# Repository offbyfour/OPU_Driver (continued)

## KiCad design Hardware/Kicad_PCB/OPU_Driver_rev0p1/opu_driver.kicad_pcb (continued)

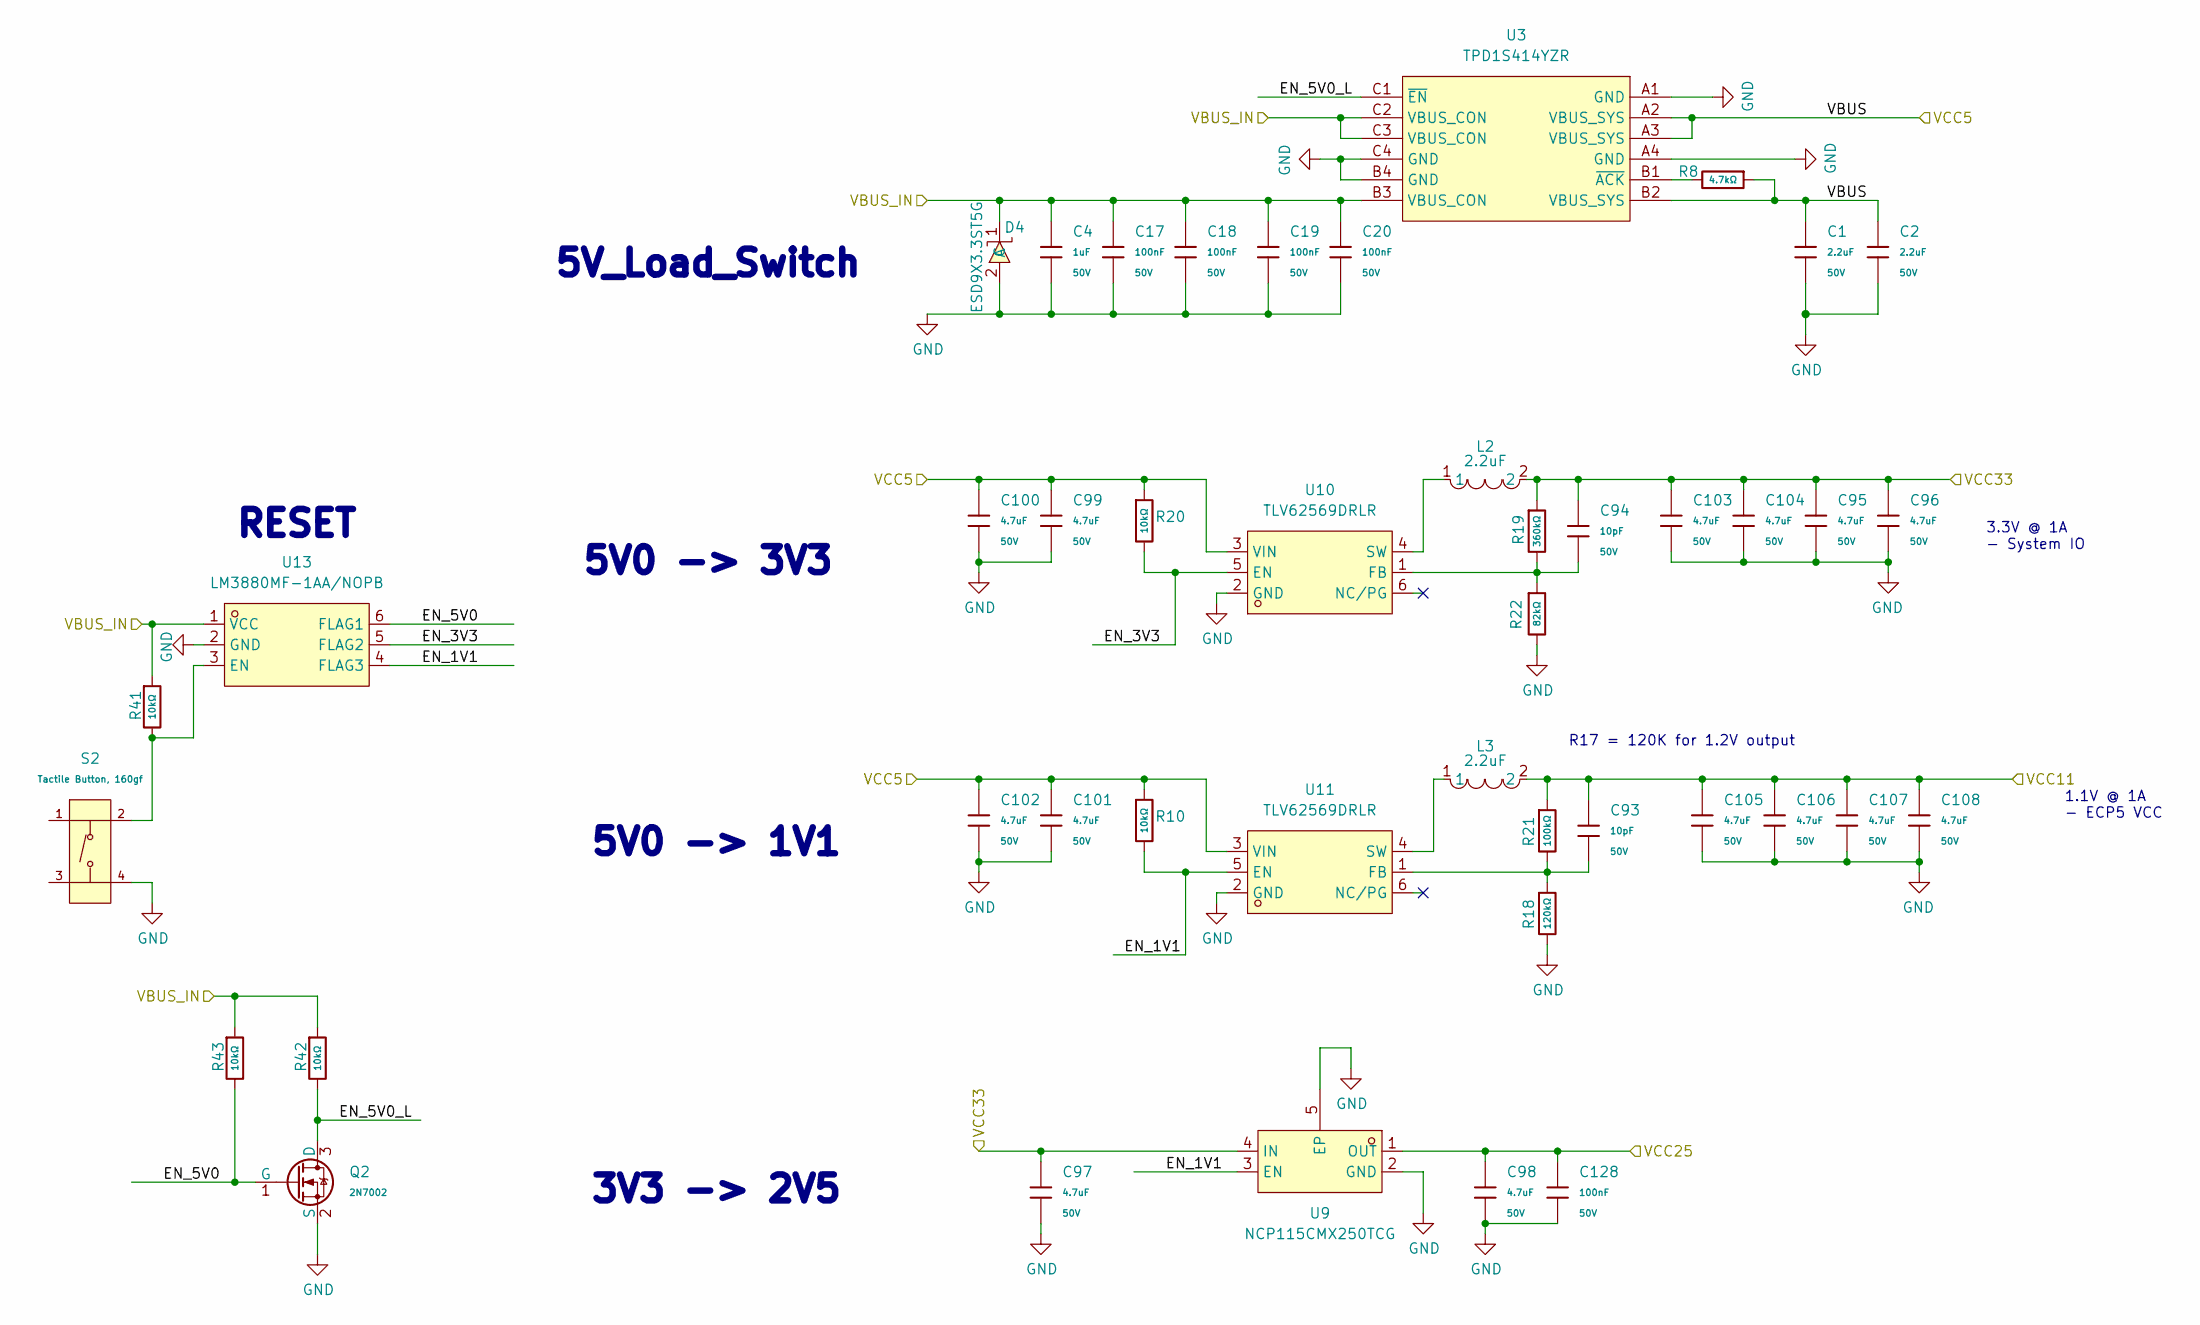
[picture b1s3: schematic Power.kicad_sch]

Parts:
C1, C2: 2.2uF; C_1206; Voltage Rated 50V; Tolerance ±10%; Part CL31B225KBHNNNE; LCSC C50254
C4: 1uF; C_0805; Voltage Rated 50V; Tolerance ±10%; Part CL21B105KBFNNNE; LCSC C28323
C17, C18, C19, C20, C128: 100nF; C_0402; Voltage Rated 50V; Tolerance ±10%; Part CL05B104KB54PNC; LCSC C307331
C93, C94: 10pF; C_0402; Voltage Rated 50V; Tolerance ±5%; Part CL05C100JB5NNNC; LCSC C32949
C95, C96, C97, C98, C99, C100, C101, C102, C103, C104, C105, C106, C107, C108: 4.7uF; C_1206; Voltage Rated 50V; Tolerance ±10%; Part 1206B475K500NT; LCSC C29823
D4: ESD9X3.3ST5G; SOD-923_L0.8-W0.6-LS1.0-RD; LCSC Part C130456
L2, L3: LQM21PN2R2NGCD; L0805; LCSC Part C86089
Q2: 2N7002; Q_SOT-23; Part 2N7002; LCSC C8545
R8: 4.7kΩ; R_0402; Overload Voltage (Max) 50V; Tolerance ±1%; Part 0402WGF4701TCE; LCSC C25900
R10, R20, R41, R42, R43: 10kΩ; R_0402; Overload Voltage (Max) 50V; Tolerance ±1%; Part 0402WGF1002TCE; LCSC C25744
R18: 120kΩ; R_0402; Overload Voltage (Max) 50V; Tolerance ±1%; Part 0402WGF1203TCE; LCSC C25750
R19: 360kΩ; R_0603; Overload Voltage (Max) 75V; Tolerance ±1%; Part 0603WAF3603T5E; LCSC C23146
R21: 100kΩ; R_0402; Overload Voltage (Max) 50V; Tolerance ±1%; Part 0402WGF1003TCE; LCSC C25741
R22: 82kΩ; R_0603; Overload Voltage (Max) 75V; Tolerance ±1%; Part 0603WAF8202T5E; LCSC C23254
S2: Tactile Button, 160gf; SW-SMD_4P-L5.1-W5.1-P3.70-LS6.5-TL-2; Voltage Rating (Dc) 12V; Part TS-1187A-B-A-B; LCSC C318884
U3: TPD1S414YZR; DSBGA-12_L1.9-W1.4-R3-C4-P0.40-TL; LCSC Part C411873
U9: NCP115CMX250TCG; XDFN-4_L1.0-W1.0-P0.65-BL-EP; LCSC Part C603508
U10, U11: TLV62569DRLR; SOT-563_L1.6-W1.2-P0.50-LS1.6-BL; LCSC Part C163217
U13: LM3880MF-1AA/NOPB; SOT-23-6_L2.9-W1.6-P0.95-LS2.8-BR; LCSC Part C486059

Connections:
+1V1: C93.1, C105.1, C106.1, C107.1, C108.1, L3.2, R21.1; also elsewhere on the board
+2V5: C98.1, C128.1, U9.1 (OUT); also elsewhere on the board
+3V3: C94.1, C95.1, C96.1, C97.1, C103.1, C104.1, L2.2, R19.1, U9.4 (IN); also elsewhere on the board
/Power/EN_1V1: R10.2, U9.3 (EN), U11.5 (EN), U13.4 (FLAG3)
/Power/EN_3V3: R20.2, U10.5 (EN), U13.5 (FLAG2)
/Power/EN_5V0: Q2.1 (G), R43.2, U13.6 (FLAG1)
/Power/EN_5V0_L: Q2.3 (D), R42.2, U3.C1 (~EN)
/VBUS: C4.1, C17.1, C18.1, C19.1, C20.1, D4.1 (C), R41.1, R42.1, R43.1, U3.B3 (VBUS_CON), U3.C2 (VBUS_CON), U3.C3 (VBUS_CON), U13.1 (VCC); also elsewhere on the board
GND: C1.2, C2.2, C4.2, C17.2, C18.2, C19.2, C20.2, C95.2, C96.2, C97.2, C98.2, C99.2, C100.2, C101.2, C102.2, C103.2, C104.2, C105.2, C106.2, C107.2, C108.2, C128.2, D4.2 (A), Q2.2 (S), R18.2, R22.2, S2.4 (D), U3.A1 (GND), U3.A4 (GND), U3.B4 (GND), U3.C4 (GND), U9.2 (GND), U9.5 (EP), U10.2 (GND), U11.2 (GND), U13.2 (GND); also elsewhere on the board
unnamed: R41.2, S2.2 (B), U13.3 (EN)
unnamed: R8.2, U3.B1 (~ACK)
unnamed: C94.2, R19.2, R22.1, U10.1 (FB)
unnamed: L2.1, U10.4 (SW)
unnamed: C93.2, R18.1, R21.2, U11.1 (FB)
unnamed: L3.1, U11.4 (SW)

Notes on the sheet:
3.3V @ 1A - System IO
5V0 -> 1V1
RESET
5V_Load_Switch
1.1V @ 1A - ECP5 VCC
5V0 -> 3V3
3V3 -> 2V5
R17 = 120K for 1.2V output

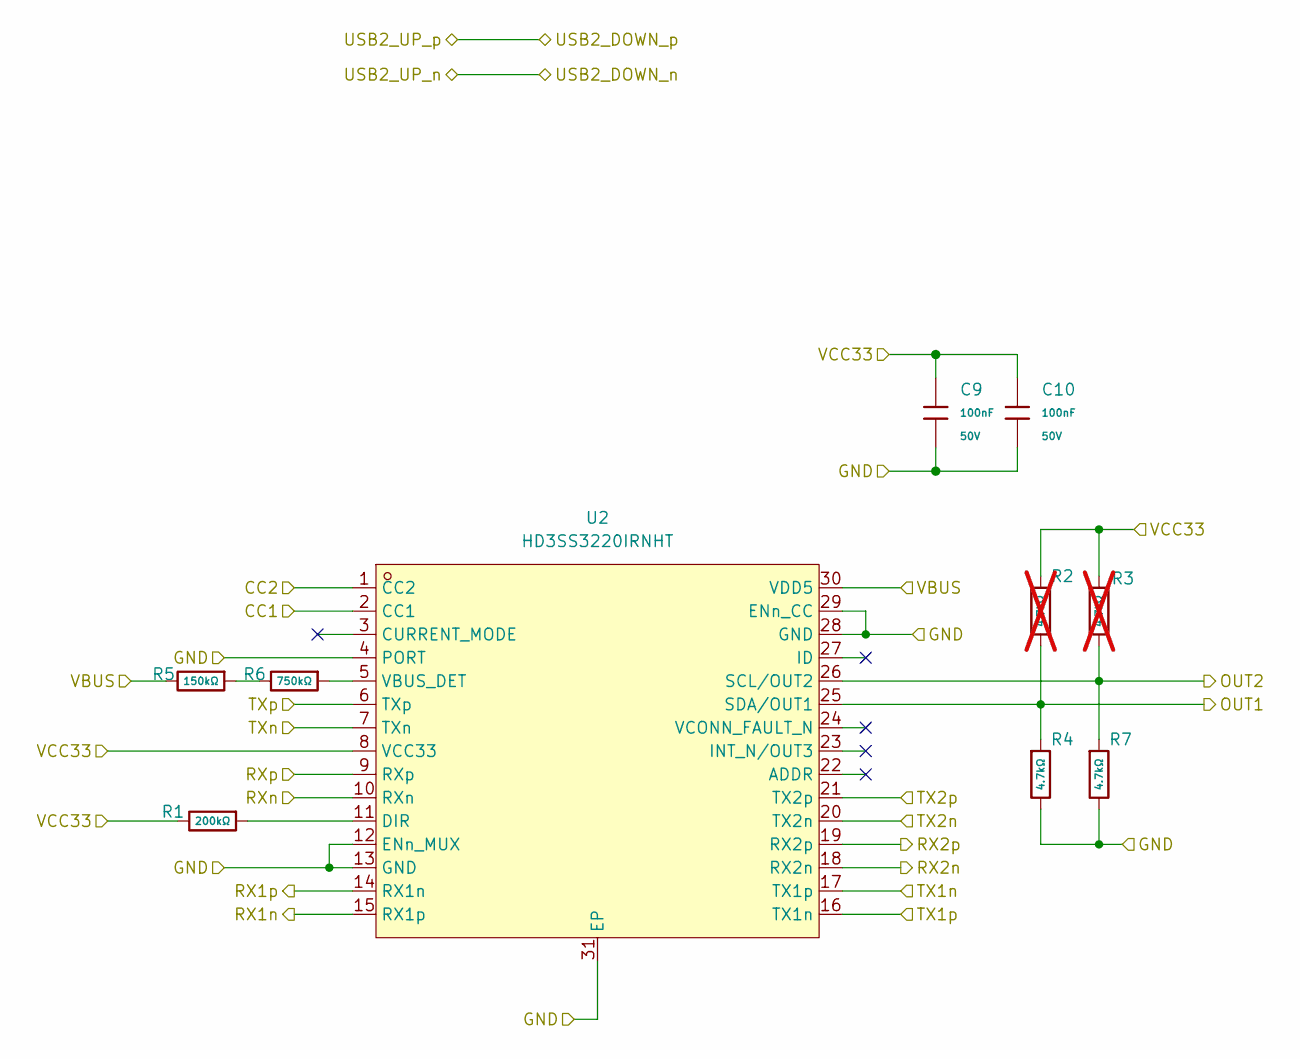
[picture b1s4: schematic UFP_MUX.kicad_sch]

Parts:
C9, C10: 100nF; C_0402; Voltage Rated 50V; Tolerance ±10%; Part CL05B104KB54PNC; LCSC C307331
R1: 200kΩ; R_0402; Overload Voltage (Max) 50V; Tolerance ±1%; Part 0402WGF2003TCE; LCSC C25764
R2, R3: 4.7kΩ; R_0402; Overload Voltage (Max) 50V; Tolerance ±1%; Part 0402WGF4701TCE; LCSC C25900; not fitted
R4, R7: 4.7kΩ; R_0402; Overload Voltage (Max) 50V; Tolerance ±1%; Part 0402WGF4701TCE; LCSC C25900
R5: 150kΩ; R_0402; Overload Voltage (Max) 50V; Tolerance ±1%; Part 0402WGF1503TCE; LCSC C25755
R6: 750kΩ; R_0603; Overload Voltage (Max) 75V; Tolerance ±1%; Part 0603WAF7503T5E; LCSC C23240
U2: HD3SS3220IRNHT; WQFN-30_L4.5-W2.5-P0.4-BL-EP; LCSC Part C2876685

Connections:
+3V3: C9.1, C10.1, R1.2, R2.1, R3.1, U2.8 (VCC33); also elsewhere on the board
/CC1: U2.2 (CC1); also elsewhere on the board
/CC2: U2.1 (CC2); also elsewhere on the board
/RX1+: U2.14 (RX1n); also elsewhere on the board
/RX1-: U2.15 (RX1p); also elsewhere on the board
/RX2+: U2.19 (RX2p); also elsewhere on the board
/RX2-: U2.18 (RX2n); also elsewhere on the board
/RXN: U2.10 (RXn); also elsewhere on the board
/RXP: U2.9 (RXp); also elsewhere on the board
/TX1_N: U2.17 (TX1p); also elsewhere on the board
/TX1_P: U2.16 (TX1n); also elsewhere on the board
/TX2_N: U2.20 (TX2n); also elsewhere on the board
/TX2_P: U2.21 (TX2p); also elsewhere on the board
/TXpre_N: U2.7 (TXn); also elsewhere on the board
/TXpre_P: U2.6 (TXp); also elsewhere on the board
/UFP_MUX/OUT1: R2.2, R4.1, U2.25 (SDA/OUT1)
/UFP_MUX/OUT2: R3.2, R7.1, U2.26 (SCL/OUT2)
GND: C9.2, C10.2, R4.2, R7.2, U2.4 (PORT), U2.12 (ENn_MUX), U2.13 (GND), U2.28 (GND), U2.29 (ENn_CC), U2.31 (EP); also elsewhere on the board
unnamed: R5.1, R6.2
unnamed: R1.1, U2.11 (DIR)
unnamed: R6.1, U2.5 (VBUS_DET)

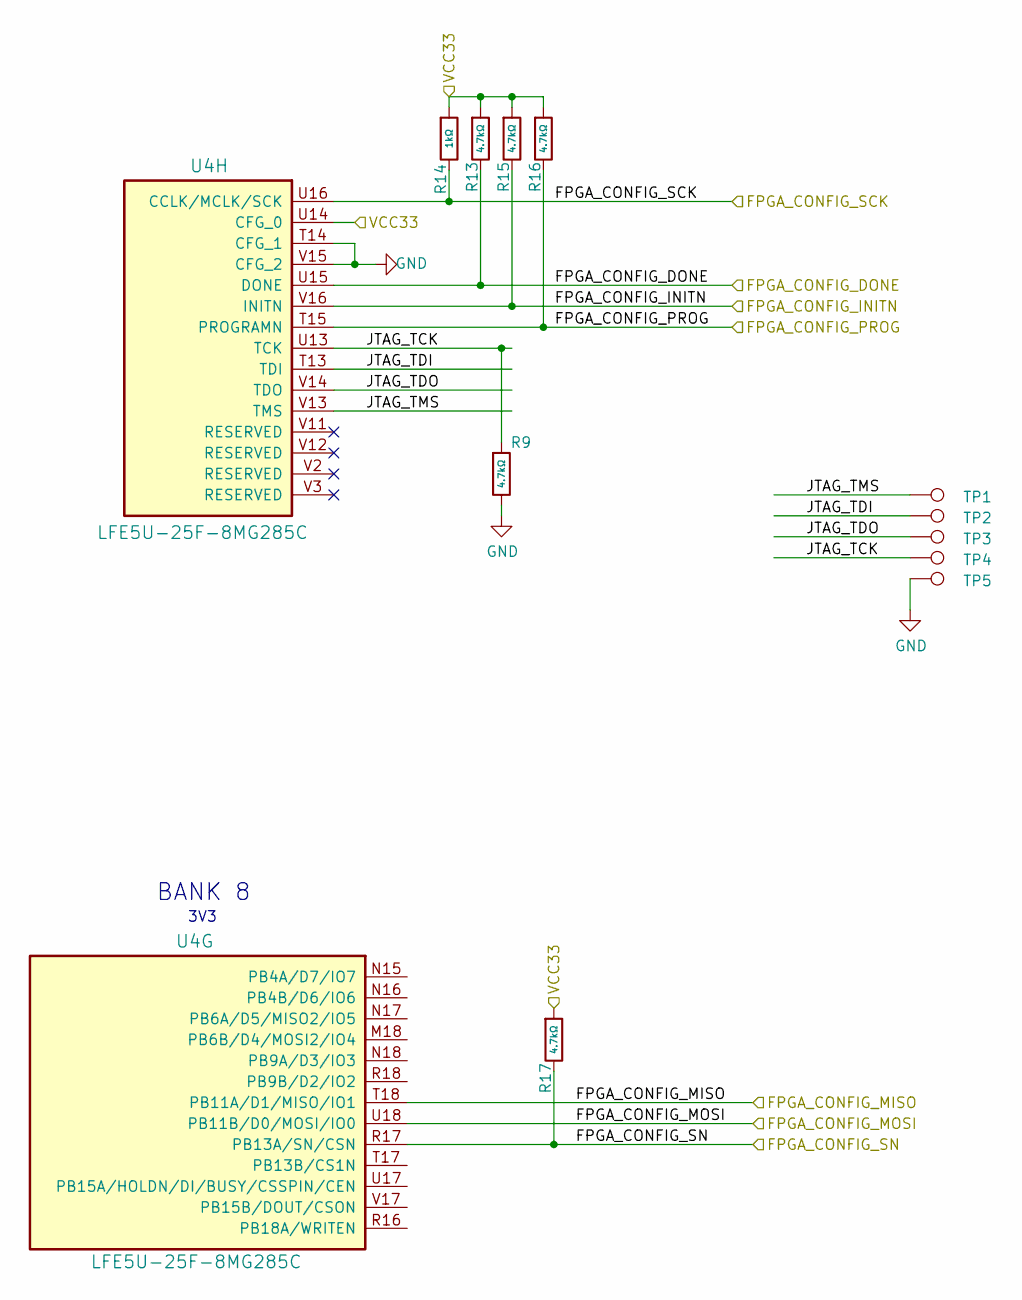
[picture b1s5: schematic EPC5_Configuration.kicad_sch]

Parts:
R9, R13, R15, R16, R17: 4.7kΩ; R_0402; Overload Voltage (Max) 50V; Tolerance ±1%; Part 0402WGF4701TCE; LCSC C25900
R14: 1kΩ; R_0402; Overload Voltage (Max) 50V; Tolerance ±1%; Part 0402WGF1001TCE; LCSC C11702
TP1, TP2, TP3, TP4, TP5: TestPoint; TestPoint_Pad_D1.0mm
U4: LFE5U-25F-8MG285C; csBGA285

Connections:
+3V3: R13.1, R14.1, R15.1, R16.1, R17.1, U4.U14 (CFG_0); also elsewhere on the board
/EPC5_Configuration/JTAG_TCK: R9.1, TP4.1, U4.U13 (TCK)
/EPC5_Configuration/JTAG_TDI: TP2.1, U4.T13 (TDI)
/EPC5_Configuration/JTAG_TDO: TP3.1, U4.V14 (TDO)
/EPC5_Configuration/JTAG_TMS: TP1.1, U4.V13 (TMS)
/FPGA_CONFIG_DONE: R13.2, U4.U15 (DONE); also elsewhere on the board
/FPGA_CONFIG_INITN: R15.2, U4.V16 (INITN); also elsewhere on the board
/FPGA_CONFIG_MISO: U4.T18 (PB11A/D1/MISO/IO1); also elsewhere on the board
/FPGA_CONFIG_MOSI: U4.U18 (PB11B/D0/MOSI/IO0); also elsewhere on the board
/FPGA_CONFIG_PROG: R16.2, U4.T15 (PROGRAMN); also elsewhere on the board
/FPGA_CONFIG_SCK: R14.2, U4.U16 (CCLK/MCLK/SCK); also elsewhere on the board
/FPGA_CONFIG_SN: R17.2, U4.R17 (PB13A/SN/CSN); also elsewhere on the board
GND: R9.2, TP5.1, U4.T14 (CFG_1), U4.V15 (CFG_2); also elsewhere on the board

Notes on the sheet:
BANK 8
3V3

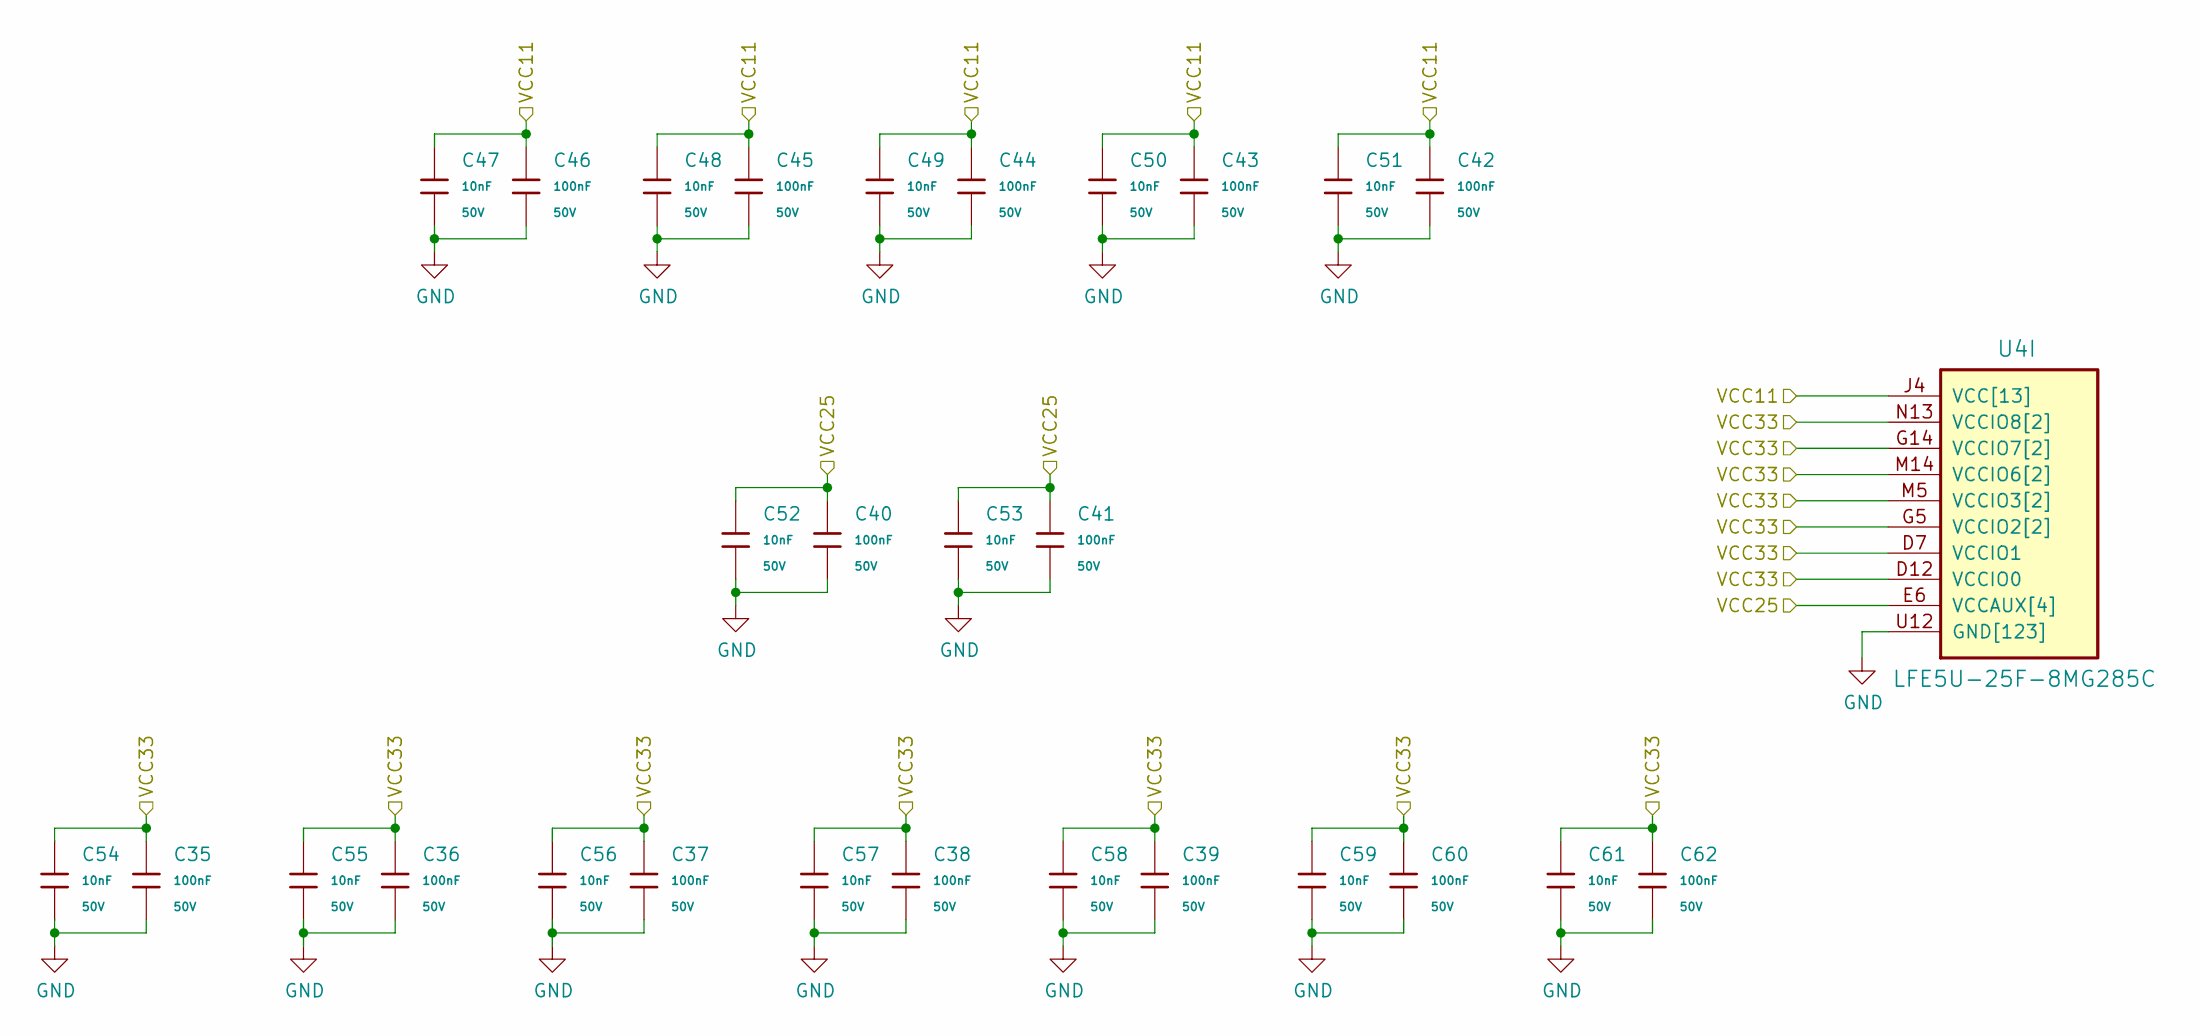
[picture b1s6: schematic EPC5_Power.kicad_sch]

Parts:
C35, C36, C37, C38, C39, C40, C41, C42, C43, C44, C45, C46, C60, C62: 100nF; C_0402; Voltage Rated 50V; Tolerance ±10%; Part CL05B104KB54PNC; LCSC C307331
C47, C48, C49, C50, C51, C52, C53, C54, C55, C56, C57, C58, C59, C61: 10nF; C_0402; Voltage Rated 50V; Tolerance ±10%; Part CL05B103KB5NNNC; LCSC C15195
U4: LFE5U-25F-8MG285C; csBGA285

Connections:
+1V1: C42.1, C43.1, C44.1, C45.1, C46.1, C47.1, C48.1, C49.1, C50.1, C51.1, U4.D8 (VCC[13]), U4.D9 (VCC[13]), U4.D10 (VCC[13]), U4.D11 (VCC[13]), U4.J4 (VCC[13]), U4.J5 (VCC[13]), U4.J14 (VCC[13]), U4.J15 (VCC[13]), U4.M4 (VCC[13]), U4.M15 (VCC[13]), U4.P7 (VCC[13]), U4.P9 (VCC[13]), U4.P11 (VCC[13]); also elsewhere on the board
+2V5: C40.1, C41.1, C52.1, C53.1, U4.E6 (VCCAUX[4]), U4.E13 (VCCAUX[4]), U4.N6 (VCCAUX[4]), U4.P13 (VCCAUX[4]); also elsewhere on the board
+3V3: C35.1, C36.1, C37.1, C38.1, C39.1, C54.1, C55.1, C56.1, C57.1, C58.1, C59.1, C60.1, C61.1, C62.1, U4.D7 (VCCIO1), U4.D12 (VCCIO0), U4.G5 (VCCIO2[2]), U4.G14 (VCCIO7[2]), U4.H5 (VCCIO2[2]), U4.H14 (VCCIO7[2]), U4.M5 (VCCIO3[2]), U4.M14 (VCCIO6[2]), U4.N5 (VCCIO3[2]), U4.N13 (VCCIO8[2]), U4.N14 (VCCIO6[2]), U4.P14 (VCCIO8[2]); also elsewhere on the board
GND: C35.2, C36.2, C37.2, C38.2, C39.2, C40.2, C41.2, C42.2, C43.2, C44.2, C45.2, C46.2, C47.2, C48.2, C49.2, C50.2, C51.2, C52.2, C53.2, C54.2, C55.2, C56.2, C57.2, C58.2, C59.2, C60.2, C61.2, C62.2, U4.B3 (GND[123]), U4.B16 (GND[123]), U4.E5 (GND[123]), U4.E7 (GND[123]), U4.E8 (GND[123]), U4.E9 (GND[123]), U4.E10 (GND[123]), U4.E11 (GND[123]), U4.E12 (GND[123]), U4.E14 (GND[123]), U4.F5 (GND[123]), U4.F6 (GND[123]), U4.F7 (GND[123]), U4.F8 (GND[123]), U4.F9 (GND[123]), U4.F10 (GND[123]), U4.F11 (GND[123]), U4.F12 (GND[123]), U4.F13 (GND[123]), U4.F14 (GND[123]), U4.G2 (GND[123]), U4.G6 (GND[123]), U4.G7 (GND[123]), U4.G8 (GND[123]), U4.G9 (GND[123]), U4.G10 (GND[123]), U4.G11 (GND[123]), U4.G12 (GND[123]), U4.G13 (GND[123]), U4.G17 (GND[123]), U4.H6 (GND[123]), U4.H7 (GND[123]), U4.H8 (GND[123]), U4.H9 (GND[123]), U4.H10 (GND[123]), U4.H11 (GND[123]), U4.H12 (GND[123]), U4.H13 (GND[123]), U4.J6 (GND[123]), U4.J7 (GND[123]), U4.J8 (GND[123]), U4.J9 (GND[123]), U4.J10 (GND[123]), U4.J11 (GND[123]), U4.J12 (GND[123]), U4.J13 (GND[123]), U4.K5 (GND[123]), U4.K6 (GND[123]), U4.K7 (GND[123]), U4.K8 (GND[123]), U4.K9 (GND[123]), U4.K10 (GND[123]), U4.K11 (GND[123]), U4.K12 (GND[123]), U4.K13 (GND[123]), U4.K14 (GND[123]), U4.L2 (GND[123]), U4.L5 (GND[123]), U4.L6 (GND[123]), U4.L7 (GND[123]), U4.L8 (GND[123]), U4.L9 (GND[123]), U4.L10 (GND[123]), U4.L11 (GND[123]), U4.L12 (GND[123]), U4.L13 (GND[123]), U4.L14 (GND[123]), U4.L17 (GND[123]), U4.M6 (GND[123]), U4.M7 (GND[123]), U4.M8 (GND[123]), U4.M9 (GND[123]), U4.M10 (GND[123]), U4.M11 (GND[123]), U4.M12 (GND[123]), U4.M13 (GND[123]), U4.N7 (GND[123]), U4.N8 (GND[123]), U4.N9 (GND[123]), U4.N10 (GND[123]), U4.N11 (GND[123]), U4.N12 (GND[123]), U4.P5 (GND[123]), U4.P6 (GND[123]), U4.P8 (GND[123]), U4.P10 (GND[123]), U4.P12 (GND[123]), U4.R1 (GND[123]), U4.R2 (GND[123]), U4.R3 (GND[123]), U4.R10 (GND[123]), U4.T1 (GND[123]), U4.T2 (GND[123]), U4.T3 (GND[123]), U4.T4 (GND[123]), U4.T5 (GND[123]), U4.T6 (GND[123]), U4.T7 (GND[123]), U4.T8 (GND[123]), U4.T9 (GND[123]), U4.T10 (GND[123]), U4.T11 (GND[123]), U4.T12 (GND[123]), U4.T16 (GND[123]), U4.U1 (GND[123]), U4.U2 (GND[123]), U4.U3 (GND[123]), U4.U4 (GND[123]), U4.U5 (GND[123]), U4.U6 (GND[123]), U4.U7 (GND[123]), U4.U8 (GND[123]), U4.U9 (GND[123]), U4.U10 (GND[123]), U4.U11 (GND[123]), U4.U12 (GND[123]), U4.V4 (GND[123]), U4.V5 (GND[123]), U4.V6 (GND[123]), U4.V7 (GND[123]), U4.V8 (GND[123]), U4.V9 (GND[123]), U4.V10 (GND[123]); also elsewhere on the board

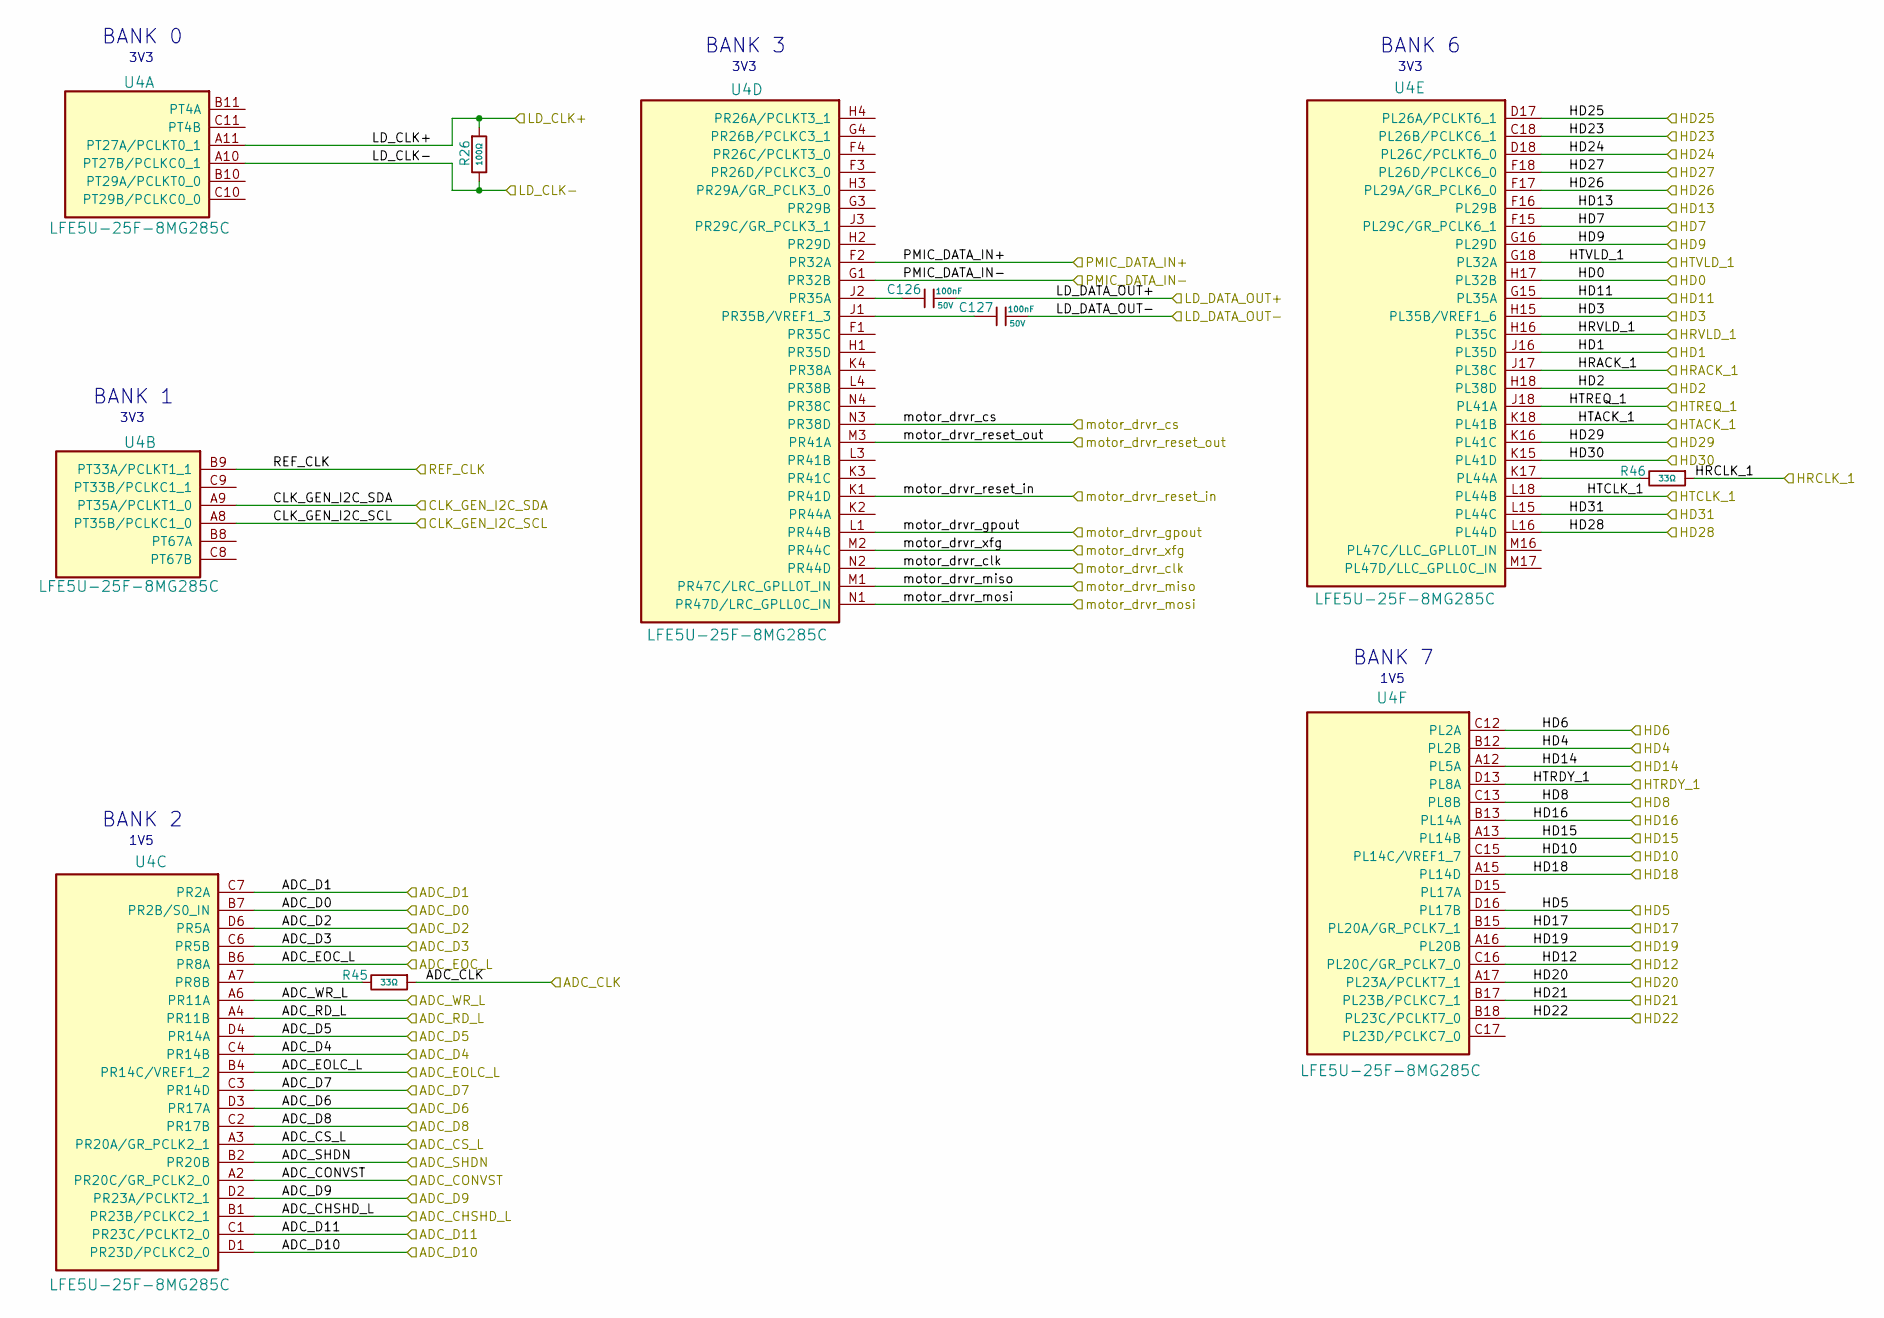
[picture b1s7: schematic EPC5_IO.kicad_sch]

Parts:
C126, C127: 100nF; C_0402; Voltage Rated 50V; Tolerance ±10%; Part CL05B104KB54PNC; LCSC C307331
R26: 100Ω; R_0402; Overload Voltage (Max) 50V; Tolerance ±1%; Part 0402WGF1000TCE; LCSC C25076
R45, R46: 33Ω; R_0402; Overload Voltage (Max) 50V; Tolerance ±1%; Part 0402WGF330JTCE; LCSC C25105
U4: LFE5U-25F-8MG285C; csBGA285

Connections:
/ADC_CHSHD_L: U4.B1 (PR23B/PCLKC2_1); also elsewhere on the board
/ADC_CLK: R45.1; also elsewhere on the board
/ADC_CONVST: U4.A2 (PR20C/GR_PCLK2_0); also elsewhere on the board
/ADC_CS_L: U4.A3 (PR20A/GR_PCLK2_1); also elsewhere on the board
/ADC_D0: U4.B7 (PR2B/S0_IN); also elsewhere on the board
/ADC_D1: U4.C7 (PR2A); also elsewhere on the board
/ADC_D2: U4.D6 (PR5A); also elsewhere on the board
/ADC_D3: U4.C6 (PR5B); also elsewhere on the board
/ADC_D4: U4.C4 (PR14B); also elsewhere on the board
/ADC_D5: U4.D4 (PR14A); also elsewhere on the board
/ADC_D6: U4.D3 (PR17A); also elsewhere on the board
/ADC_D7: U4.C3 (PR14D); also elsewhere on the board
/ADC_D8: U4.C2 (PR17B); also elsewhere on the board
/ADC_D9: U4.D2 (PR23A/PCLKT2_1); also elsewhere on the board
/ADC_D10: U4.D1 (PR23D/PCLKC2_0); also elsewhere on the board
/ADC_D11: U4.C1 (PR23C/PCLKT2_0); also elsewhere on the board
/ADC_EOC_L: U4.B6 (PR8A); also elsewhere on the board
/ADC_EOLC_L: U4.B4 (PR14C/VREF1_2); also elsewhere on the board
/ADC_RD_L: U4.A4 (PR11B); also elsewhere on the board
/ADC_SHDN: U4.B2 (PR20B); also elsewhere on the board
/ADC_WR_L: U4.A6 (PR11A); also elsewhere on the board
/CLK_GEN_I2C_SCL: U4.A8 (PT35B/PCLKC1_0); also elsewhere on the board
/CLK_GEN_I2C_SDA: U4.A9 (PT35A/PCLKT1_0); also elsewhere on the board
/HD0: U4.H17 (PL32B); also elsewhere on the board
/HD1: U4.J16 (PL35D); also elsewhere on the board
/HD2: U4.H18 (PL38D); also elsewhere on the board
/HD3: U4.H15 (PL35B/VREF1_6); also elsewhere on the board
/HD4: U4.B12 (PL2B); also elsewhere on the board
/HD5: U4.D16 (PL17B); also elsewhere on the board
/HD6: U4.C12 (PL2A); also elsewhere on the board
/HD7: U4.F15 (PL29C/GR_PCLK6_1); also elsewhere on the board
/HD8: U4.C13 (PL8B); also elsewhere on the board
/HD9: U4.G16 (PL29D); also elsewhere on the board
/HD10: U4.C15 (PL14C/VREF1_7); also elsewhere on the board
/HD11: U4.G15 (PL35A); also elsewhere on the board
/HD12: U4.C16 (PL20C/GR_PCLK7_0); also elsewhere on the board
/HD13: U4.F16 (PL29B); also elsewhere on the board
/HD14: U4.A12 (PL5A); also elsewhere on the board
/HD15: U4.A13 (PL14B); also elsewhere on the board
/HD16: U4.B13 (PL14A); also elsewhere on the board
/HD17: U4.B15 (PL20A/GR_PCLK7_1); also elsewhere on the board
/HD18: U4.A15 (PL14D); also elsewhere on the board
/HD19: U4.A16 (PL20B); also elsewhere on the board
/HD20: U4.A17 (PL23A/PCLKT7_1); also elsewhere on the board
/HD21: U4.B17 (PL23B/PCLKC7_1); also elsewhere on the board
/HD22: U4.B18 (PL23C/PCLKT7_0); also elsewhere on the board
/HD23: U4.C18 (PL26B/PCLKC6_1); also elsewhere on the board
/HD24: U4.D18 (PL26C/PCLKT6_0); also elsewhere on the board
/HD25: U4.D17 (PL26A/PCLKT6_1); also elsewhere on the board
/HD26: U4.F17 (PL29A/GR_PCLK6_0); also elsewhere on the board
/HD27: U4.F18 (PL26D/PCLKC6_0); also elsewhere on the board
/HD28: U4.L16 (PL44D); also elsewhere on the board
/HD29: U4.K16 (PL41C); also elsewhere on the board
/HD30: U4.K15 (PL41D); also elsewhere on the board
/HD31: U4.L15 (PL44C); also elsewhere on the board
/HRACK_1: U4.J17 (PL38C); also elsewhere on the board
/HRCLK_1: R46.1; also elsewhere on the board
/HRVLD_1: U4.H16 (PL35C); also elsewhere on the board
/HTACK_1: U4.K18 (PL41B); also elsewhere on the board
/HTCLK_1: U4.L18 (PL44B); also elsewhere on the board
/HTRDY_1: U4.D13 (PL8A); also elsewhere on the board
/HTREQ_1: U4.J18 (PL41A); also elsewhere on the board
/HTVLD_1: U4.G18 (PL32A); also elsewhere on the board
/LD_CLK+: R26.1, U4.A11 (PT27A/PCLKT0_1); also elsewhere on the board
/LD_CLK-: R26.2, U4.A10 (PT27B/PCLKC0_1); also elsewhere on the board
/LD_DATA_OUT+: C126.2; also elsewhere on the board
/LD_DATA_OUT-: C127.2; also elsewhere on the board
/PMIC_DATA_IN+: U4.F2 (PR32A); also elsewhere on the board
/PMIC_DATA_IN-: U4.G1 (PR32B); also elsewhere on the board
/motor_drvr_clk: U4.N2 (PR44D); also elsewhere on the board
/motor_drvr_cs: U4.N3 (PR38D); also elsewhere on the board
/motor_drvr_gpout: U4.L1 (PR44B); also elsewhere on the board
/motor_drvr_miso: U4.M1 (PR47C/LRC_GPLL0T_IN); also elsewhere on the board
/motor_drvr_mosi: U4.N1 (PR47D/LRC_GPLL0C_IN); also elsewhere on the board
/motor_drvr_reset_in: U4.K1 (PR41D); also elsewhere on the board
/motor_drvr_reset_out: U4.M3 (PR41A); also elsewhere on the board
/motor_drvr_xfg: U4.M2 (PR44C); also elsewhere on the board
/ref_clk: U4.B9 (PT33A/PCLKT1_1); also elsewhere on the board
unnamed: R45.2, U4.A7 (PR8B)
unnamed: C126.1, U4.J2 (PR35A)
unnamed: C127.1, U4.J1 (PR35B/VREF1_3)
unnamed: R46.2, U4.K17 (PL44A)

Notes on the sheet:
BANK 2
BANK 1
BANK 7
3V3
1V5
3V3
BANK 6
BANK 0
BANK 3

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
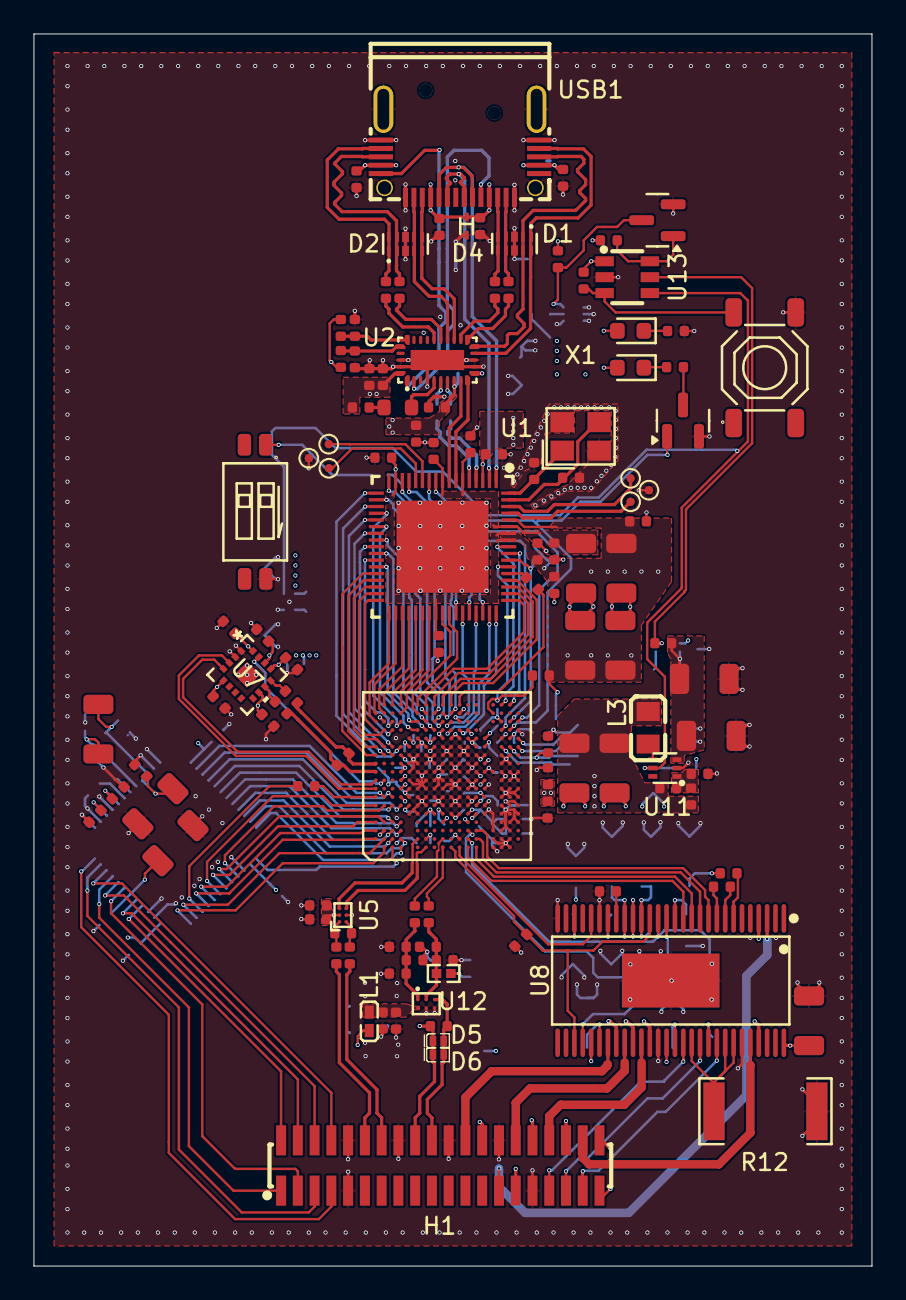
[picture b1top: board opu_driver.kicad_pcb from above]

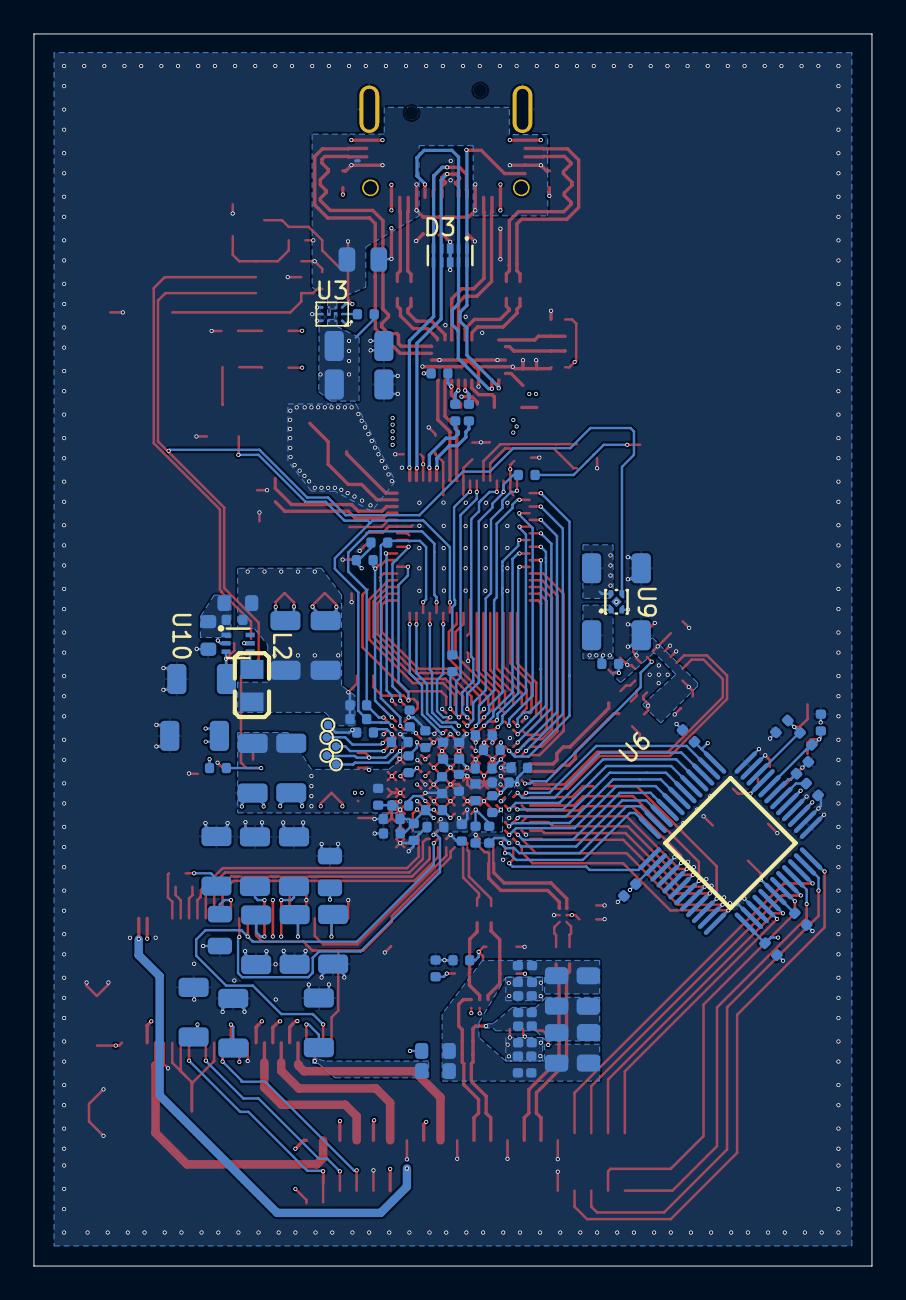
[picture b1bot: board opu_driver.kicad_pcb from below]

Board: 4 copper layers, 50.0 x 73.5 mm, 218 parts (99 on the bottom side), 193 nets.

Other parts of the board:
C7#2: 10pF; C_0402
C8#2: 100nF; C_0402

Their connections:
GND: C7#2.2, C8#2.2; also elsewhere on the board

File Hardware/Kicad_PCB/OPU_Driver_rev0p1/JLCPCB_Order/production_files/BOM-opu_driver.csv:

Comment,Designator,Footprint,LCSC,Quantity
1kΩ,"R14,R28",R_0402,C11702,2
ESD9X3.3ST5G,D4,SOD-923_L0.8-W0.6-LS1.0-RD,C130456,1
10nF,"C47,C48,C49,C50,C51,C52,C53,C54,C55,C56,C57,C58,C59,C61,C72,C73",C_0402,C15195,16
TLV62569DRLR,"U10,U11",SOT-563_L1.6-W1.2-P0.50-LS1.6-BL,C163217,2
RC0402FR-071K8L,R27,R0402,C163481,1
0Ω,"R23,R24,R25",R_0402,C17168,3
0Ω,"R38,R39",R_0603,C21189,2
White,D9,D_0603,C2290,1
360kΩ,R19,R_0603,C23146,1
750kΩ,R6,R_0603,C23240,1
82kΩ,R22,R_0603,C23254,1
100Ω,R26,R_0402,C25076,1
33Ω,"R44,R45,R46",R_0402,C25105,3
51Ω,"R29,R30",R_0402,C25125,2
1Ω,"R31,R32,R33,R34",R_0805,C25271,4
X1E0000210295,X1,CRYSTAL-SMD_4P-L3.2-W2.5-BL,C255930,1
100kΩ,R21,R_0402,C25741,1
10kΩ,"R10,R20,R35,R41,R42,R43",R_0402,C25744,6
120kΩ,R18,R_0402,C25750,1
150kΩ,R5,R_0402,C25755,1
200kΩ,R1,R_0402,C25764,1
4.7kΩ,"R11,R13,R15,R16,R17,R3,R4,R40,R7,R8,R9",R_0402,C25900,11
MAX1304ECM+T,U6,TQFP-48_L7.0-W7.0-P0.50-LS9.0-BL,C2670670,1
GT-USB-7018,USB1,TYPE-C-SMD_GT-USB-7018,C2762978,1
1uF,"C4,C81,C90",C_0805,C28323,3
CH569W,U1,QFN-68_L8.0-W8.0-P0.40-BL-EP5.5,C2857462,1
HD3SS3220IRNHT,U2,WQFN-30_L4.5-W2.5-P0.4-BL-EP,C2876685,1
DIP Switch x 2,S1,SW-SMD_218-2LPSTRF,C2961921,1
4.7uF,"C100,C101,C102,C103,C104,C105,C106,C107,C108,C3,C5,C79,C80,C82,C83,C84,C85,C86,C87,C88,C89,C95,C96,C97,C98,C99",C_1206,C29823,26
Green,D7,D_0603,C2986059,1
6pF,C117,C_0402,C30274,1
100nF,"C10,C109,C11,C110,C111,C112,C113,C114,C115,C116,C118,C119,C12,C120,C121,C122,C123,C124,C125,C126,C127,C128,C13,C14,C15,C16,C17,C18,C19,C20,C21,C22,C23,C24,C25,C26,C27,C28,C29,C30,C31,C32,C33,C34,C35,C36,C37,C38,C39,C40,C41,C42,C43,C44,C45,C46,C60,C62,C63,C64,C65,C67,C68,C69,C70,C74,C75,C76,C77,C78,C8,C9,C92",C_0402,C307331,73
"Tactile Button, 160gf",S2,SW-SMD_4P-L5.1-W5.1-P3.70-LS6.5-TL-2,C318884,1
10pF,"C6,C7,C93,C94",C_0402,C32949,4
2kΩ,"R36,R37",R_0402,C4109,2
TPD1S414YZR,U3,DSBGA-12_L1.9-W1.4-R3-C4-P0.40-TL,C411873,1
ZX-PM1.0-2-20PU-W,H1,HDR-SMD_40P-P1.00-V-F-R2-C20-LS3.8,C41369836,1
LM3880MF-1AA/NOPB,U13,SOT-23-6_L2.9-W1.6-P0.95-LS2.8-BR,C486059,1
2.2uF,"C1,C2,C66,C71,C91",C_1206,C50254,5
CR2512J1R220G,R12,R2512,C5381546,1
PMEG6010AESBYL,"D5,D6",X1SON-2_L1.0-W0.6-P0.65-RD,C552929,2
BLM15EX331SN1D,L1,L0402,C596498,1
NCP115CMX250TCG,U9,XDFN-4_L1.0-W1.0-P0.65-BL-EP,C603508,1
ESD8004MUTAG,"D1,D2,D3",UDFN-10_L2.5-W1.0-P0.50-BL,C605399,3
EPC21603,U12,BGA-6_L1.5-W1.0-P0.50-TL,C6191277,1
TPIC2010RDFDRG4,U8,HTSSOP-56_L14.0-W6.0-P0.50-LS8.1-BL-EP,C702134,1
MAX40025CAWT+T,U5,WLP-6_L1.2-W0.8-R2-C3-P0.40-TL_MAX40111ANT,C7451830,1
2N7002,"Q1,Q2",Q_SOT-23,C8545,2
LQM21PN2R2NGCD,"L2,L3",L0805,C86089,2
TestPoint,TP11,TestPoint_Pad_D1.0mm,,1
LMK3H0102A014RERT,U7,TQFN16_RER_TEX,,1
TestPoint,TP6,TestPoint_Pad_D1.0mm,,1
TestPoint,TP8,TestPoint_Pad_D1.0mm,,1
TestPoint,TP10,TestPoint_Pad_D1.0mm,,1
TestPoint,TP7,TestPoint_Pad_D1.0mm,,1
TestPoint,TP9,TestPoint_Pad_D1.0mm,,1
LFE5U-25F-8MG285C,U4,csBGA285,,1
TestPoint,TP1,TestPoint_Pad_D1.0mm,,1
TestPoint,TP5,TestPoint_Pad_D1.0mm,,1
TestPoint,TP4,TestPoint_Pad_D1.0mm,,1
TestPoint,TP2,TestPoint_Pad_D1.0mm,,1
TestPoint,TP3,TestPoint_Pad_D1.0mm,,1

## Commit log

2025-03-20 Rename readme.md to README.md
